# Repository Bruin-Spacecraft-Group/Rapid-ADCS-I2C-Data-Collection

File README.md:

# Rapid-ACDS-I2C-Data-Collection

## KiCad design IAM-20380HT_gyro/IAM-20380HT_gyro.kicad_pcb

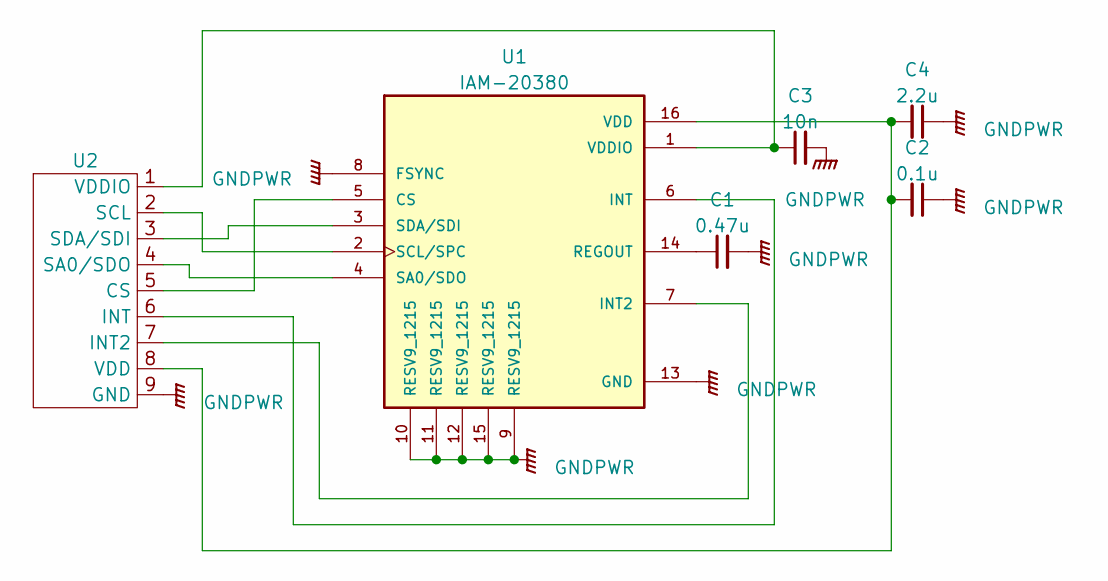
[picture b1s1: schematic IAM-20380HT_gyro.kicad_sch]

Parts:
C1: 0.47u; C_0603_1608Metric
C2: 0.1u; C_0603_1608Metric
C3: 10n; C_0603_1608Metric
C4: 2.2u; C_0603_1608Metric
U1: IAM-20380; PQFN50P300X300X80-16N
U2: PinHeader_1x09_P2.54mm_Vertical

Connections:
GNDPWR: C1.2, C2.1, C3.2, C4.1, U1.8 (FSYNC), U1.9 (RESV9_1215), U1.10 (RESV9_1215), U1.11 (RESV9_1215), U1.12 (RESV9_1215), U1.13 (GND), U1.15 (RESV9_1215), U2.9 (GND)
unnamed: U1.5 (CS), U2.5 (CS)
unnamed: U1.7 (INT2), U2.7 (INT2)
unnamed: U1.6 (INT), U2.6 (INT)
unnamed: C1.1, U1.14 (REGOUT)
unnamed: U1.4 (SA0/SDO), U2.4 (SA0/SDO)
unnamed: U1.2 (SCL/SPC), U2.2 (SCL)
unnamed: U1.3 (SDA/SDI), U2.3 (SDA/SDI)
unnamed: C2.2, C4.2, U1.16 (VDD), U2.8 (VDD)
unnamed: C3.1, U1.1 (VDDIO), U2.1 (VDDIO)

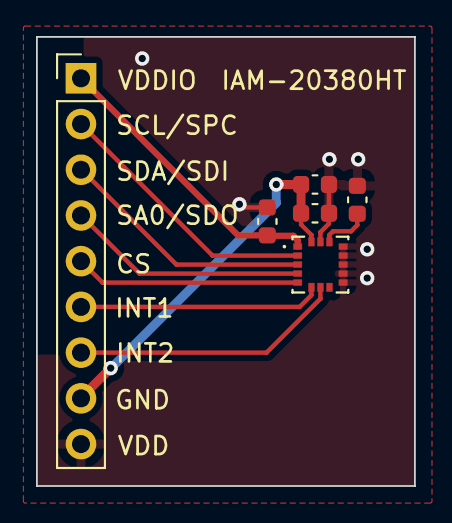
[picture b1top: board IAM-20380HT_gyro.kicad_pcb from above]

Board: 2 copper layers, 21.0 x 24.9 mm, 6 parts (0 on the bottom side), 10 nets.

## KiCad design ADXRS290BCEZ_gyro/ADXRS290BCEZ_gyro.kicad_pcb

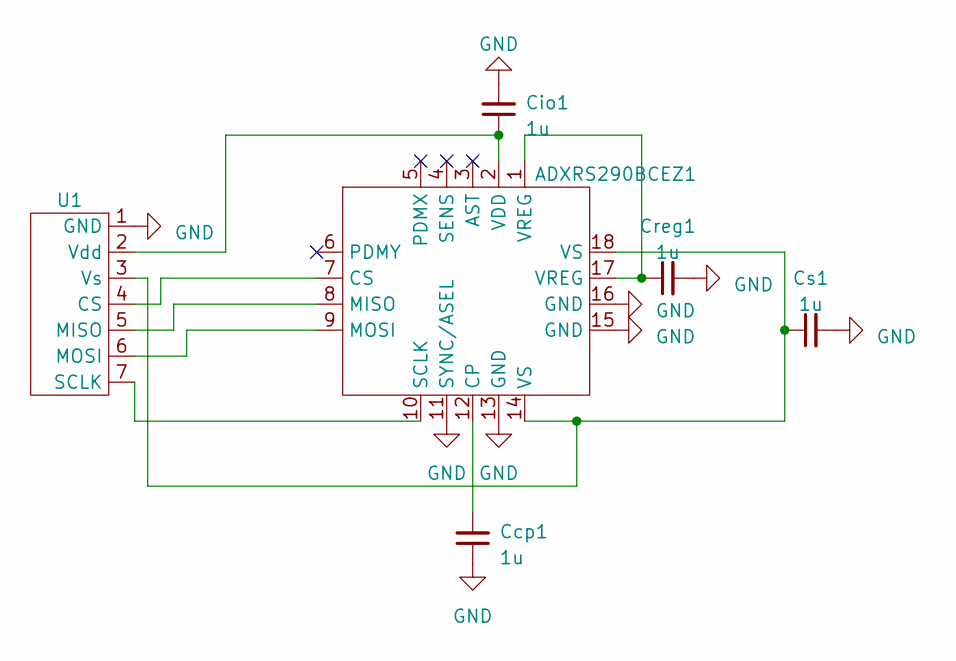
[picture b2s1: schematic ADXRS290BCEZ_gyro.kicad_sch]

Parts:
ADXRS290BCEZ1: 18-LFLGA
Ccp1: 1u; C_0603_1608Metric
Cio1: 1u; C_0603_1608Metric
Creg1: 1u; C_0603_1608Metric
Cs1: 1u; C_0603_1608Metric
U1: PinHeader_1x07_P2.54mm_Vertical

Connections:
GND: ADXRS290BCEZ1.11 (SYNC/ASEL), ADXRS290BCEZ1.13 (GND), ADXRS290BCEZ1.15 (GND), ADXRS290BCEZ1.16 (GND), Ccp1.1, Cio1.2, Creg1.2, Cs1.2, U1.1 (GND)
unnamed: ADXRS290BCEZ1.12 (CP), Ccp1.2
unnamed: ADXRS290BCEZ1.7 (CS), U1.4 (CS)
unnamed: ADXRS290BCEZ1.8 (MISO), U1.5 (MISO)
unnamed: ADXRS290BCEZ1.9 (MOSI), U1.6 (MOSI)
unnamed: ADXRS290BCEZ1.10 (SCLK), U1.7 (SCLK)
unnamed: ADXRS290BCEZ1.2 (VDD), Cio1.1, U1.2 (Vdd)
unnamed: ADXRS290BCEZ1.1 (VREG), ADXRS290BCEZ1.17 (VREG), Creg1.1
unnamed: ADXRS290BCEZ1.14 (VS), ADXRS290BCEZ1.18 (VS), Cs1.1, U1.3 (Vs)

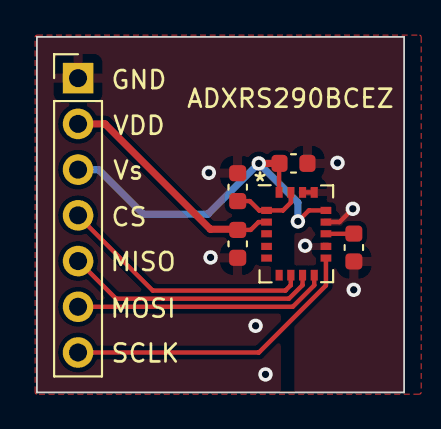
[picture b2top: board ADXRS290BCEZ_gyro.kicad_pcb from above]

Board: 2 copper layers, 20.4 x 19.8 mm, 6 parts (0 on the bottom side), 9 nets.

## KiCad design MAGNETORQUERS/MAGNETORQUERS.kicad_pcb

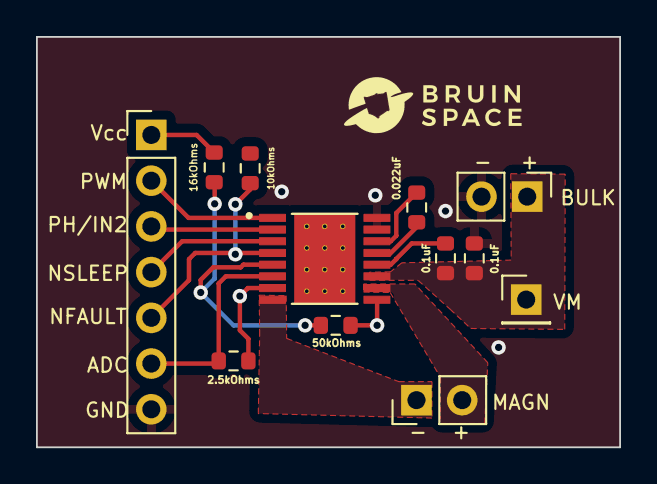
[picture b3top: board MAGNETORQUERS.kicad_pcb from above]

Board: 2 copper layers, 32.4 x 22.8 mm, 12 parts (0 on the bottom side), 14 nets.

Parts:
0.1uF, 0.1uF#2: 0.1 uF; R_0603_1608Metric
0.022uF: 0.022 uF; R_0603_1608Metric
2.5kOhms: 2.5kO; R_0603_1608Metric
10kOhms: 10kO; R_0603_1608Metric
16kOhms: 16kO; R_0603_1608Metric
50kOhms: 50kO; R_0603_1608Metric
BULKCAP1: PinHeader_1x02_P2.54mm_Vertical
MAGN: PinHeader_1x02_P2.54mm_Vertical
STM: PinHeader_1x07_P2.54mm_Vertical
U1: DRV8876PWPR; IC_DRV8876PWPR
VM1: PinHeader_1x01_P2.54mm_Vertical

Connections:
Earth: 0.1uF#2.2, 2.5kOhms.2, 50kOhms.2, BULKCAP1.2 (OUT), STM.7 (GND), U1.7 (IMODE), U1.9 (PGND), U1.15 (GND), U1.16 (PMODE)
unnamed: 0.1uF.1, 0.1uF#2.1, BULKCAP1.1 (IN), U1.11 (VM), VM1.1
unnamed: MAGN.1 (SIDE1), U1.8 (OUT1)
unnamed: MAGN.2 (SIDE2), U1.10 (OUT2)
unnamed: 2.5kOhms.1, STM.6 (ADC), U1.6 (IPROPI)
unnamed: STM.2 (PWM), U1.1 (EN/IN1)
unnamed: 10kOhms.2, 16kOhms.2, STM.1 (Vcc)
unnamed: 0.022uF.1, U1.13 (CPH)
unnamed: 0.022uF.2, U1.14 (CPL)
unnamed: STM.4 (I/O), U1.3 (NSLEEP)
unnamed: STM.3 (I/O), U1.2 (PH/IN2)
unnamed: 0.1uF.2, U1.12 (VCP)
unnamed: 16kOhms.1, 50kOhms.1, U1.5 (VREF)
unnamed: 10kOhms.1, STM.5 (I/O), U1.4 (~NFAULT)

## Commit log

2023-03-13 BNO055
2023-03-23 added functionality to print numbers and text from the stm32
2023-03-23 updated BNO055 code to be capable of reading x-acceleration data
    - removed old i2c code
    - used new function MEM READ to read instead of old functions
    - wrote to the operation mode address to get it to run
2023-03-23 finalized bno055
2023-03-24 added some things
2023-03-27 did some stuff
2023-04-04 created um7 project
2023-04-04 created gitignore
2023-04-04 changed um7 to spi
2023-04-04 created initial spi code
2023-04-04 fixed byte bitshift direction in data read
2023-04-04 updated some stuff
2023-04-05 BMX160 Code w/ Buffers
2023-04-05 updated some stuff apparently
2023-04-07 updated print function, did some stuff
2023-04-07 added gitignore file
2023-04-07 got rid of main metadata folder
2023-04-14 created a thing
2023-04-14 hehe
2023-04-22 mpu code
2023-04-25 attempted to revive mpu-6881 but it didn't work
2023-04-26 did some things idk
2023-04-26 stuff
2023-05-31 created iam-20380ht pcb
2023-05-31 added thermal reliefs and label to iam
2023-05-31 vyooed gerbers
2023-05-31 created initial symbol and footprint for ADXRS290BCEZ
2023-05-31 made some pcbs
2023-06-02 pcb stuff
2023-06-08 flatsat stuff
2023-06-08 created gerber stuff
2023-06-09 wrote some testing code
2023-06-19 iam-20380ht
2023-06-22 ahhh
2023-08-10 moved to sensors code
2023-08-10 move ADXRS290BCEZ pcb stuff to sensor board folder
2023-08-10 BNO055 moved to sensor code
2023-08-10 moved IAM
